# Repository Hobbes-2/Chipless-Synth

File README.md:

A cool chipless synth PCB! Made for the Chipless ysws.

Pictures:

BOM:

|Index|Quantity|Part Number     |Manufacturer Part Number|Description                    |Customer Reference|Available|Backorder|Unit Price|Extended Price USD|Link                                                                                                         |
|-----|--------|----------------|------------------------|-------------------------------|------------------|---------|---------|----------|------------------|-------------------------------------------------------------------------------------------------------------|
|1    |3       |4878-2N3904CT-ND|2N3904                  |TRANS NPN 40V 0.2A TO-92       |                  |3        |0        |0.14      |0.42              |https://www.digikey.com/en/products/detail/diotec-semiconductor/2N3904/13164701                              |
|2    |1       |CP-3523SJCT-ND  |SJ-3523-SMT-TR          |CONN JACK STEREO 3.5MM SMD R/A |                  |1        |0        |0.88      |0.88              |https://www.digikey.com/en/products/detail/same-sky-formerly-cui-devices/SJ-3523-SMT-TR/281297               |
|3    |1       |277-1247-ND     |1729128                 |TERM BLK 2P SIDE ENT 5.08MM PCB|                  |1        |0        |0.95      |0.95              |https://www.digikey.com/en/products/detail/phoenix-contact/1729128/260615                                    |
|4    |3       |445-2510-1-ND   |C1608X8R2A103K080AA     |CAP CER 10000PF 100V X8R 0603  |                  |3        |0        |0.14      |0.42              |https://www.digikey.com/en/products/detail/tdk/C1608X8R2A103K080AA/927136                                    |
|5    |1       |587-6004-1-ND   |EMK107B7104KAHT         |CAP CER 0.1UF 16V X7R 0603     |                  |1        |0        |0.1       |0.1               |https://www.digikey.com/en/products/detail/taiyo-yuden/EMK107B7104KAHT/7404019                               |
|6    |1       |311-4.70KMCT-ND |RC0201FR-074K7L         |RES 4.7K OHM 1% 1/20W 0201     |                  |1        |0        |0.1       |0.1               |https://www.digikey.com/en/products/detail/yageo/RC0201FR-074K7L/1948894                                     |
|7    |3       |YAG3413CT-ND    |AC0201FR-0710KL         |RES SMD 10K OHM 1% 1/20W 0201  |                  |3        |0        |0.1       |0.3               |https://www.digikey.com/en/products/detail/yageo/AC0201FR-0710KL/5894228                                     |
|8    |1       |987-1708-ND     |P0915N-EC15BR100K       |POT 100K OHM 1/20W PLASTIC LIN |                  |1        |0        |2.83      |2.83              |https://www.digikey.com/en/products/detail/tt-electronics-bi/P0915N-EC15BR100K/5957452?utm_source=chatgpt.com|
|9    |1       |401-1999-1-ND   |JS102011SAQN            |SWITCH SLIDE SPDT 300MA 6V     |                  |1        |0        |0.85      |0.85              |https://www.digikey.com/en/products/detail/c-k/JS102011SAQN/1640095?utm_source=chatgpt.com                   |

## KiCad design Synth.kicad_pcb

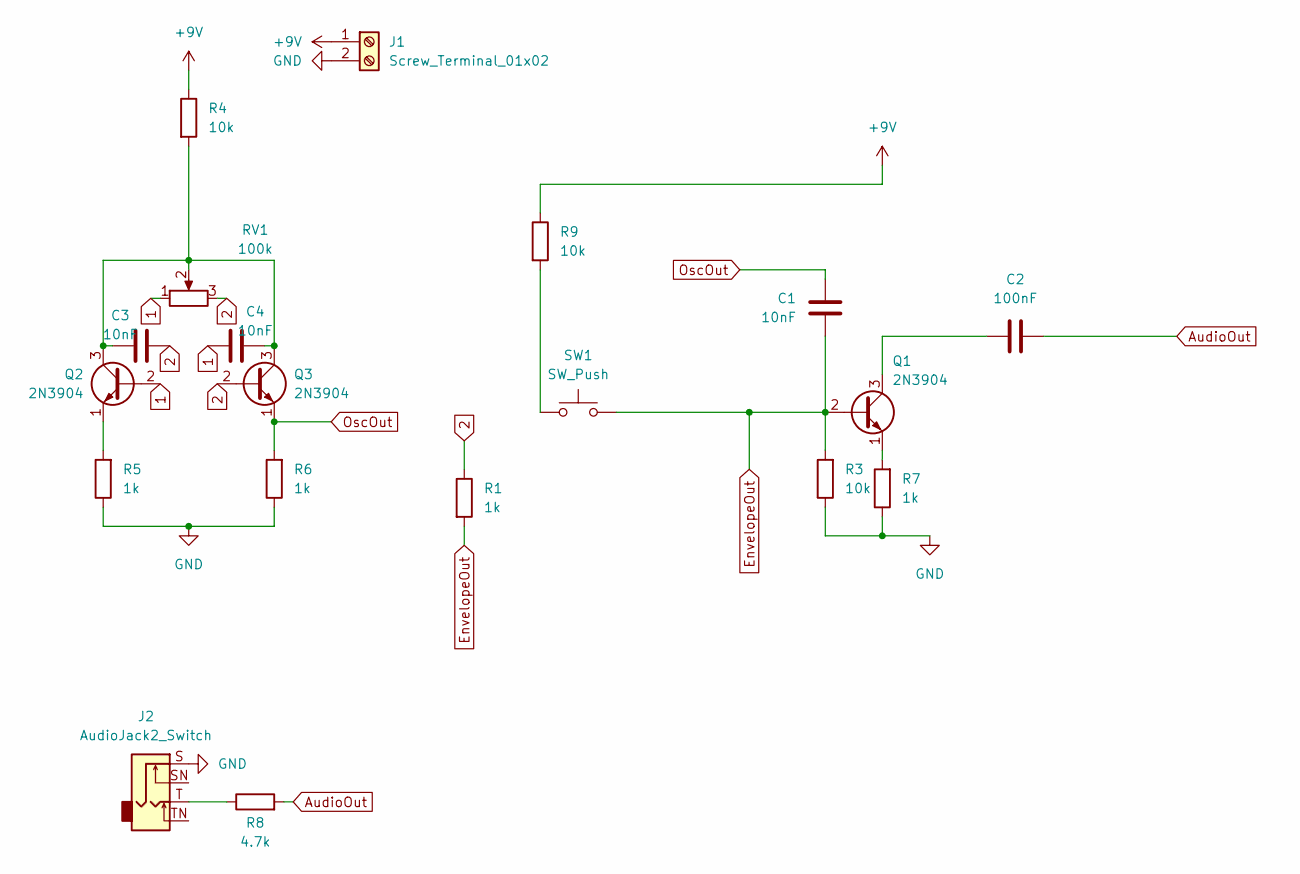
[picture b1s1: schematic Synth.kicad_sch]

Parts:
C1, C3, C4: 10nF; C_0603_1608Metric
C2: 100nF; C_0603_1608Metric
J1: Screw_Terminal_01x02; TerminalBlock_Phoenix_PT-1,5-2-5.0-H_1x02_P5.00mm_Horizontal
J2: AudioJack2_Switch; Jack_3.5mm_CUI_SJ-3523-SMT_Horizontal
Q1, Q2, Q3: 2N3904; TO-92_Inline
R1, R5, R6, R7: 1k; R_0201_0603Metric
R3, R4, R9: 10k; R_0201_0603Metric
R8: 4.7k; R_0201_0603Metric
RV1: 100k; Potentiometer_TT_P0915N
SW1: SW_Push; SW_SPDT_CK_JS102011SAQN

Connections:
1: C4.2, Q2.2 (B), RV1.1
2: C3.1, Q3.2 (B), R1.1, RV1.3
+9V: J1.1, R4.1, R9.1
AudioOut: C2.2, R8.2
EnvelopeOut: C1.2, Q1.2 (B), R1.2, R3.2, SW1.2
GND: J1.2, J2.S, R3.1, R5.1, R6.1, R7.1
unnamed: J2.T, R8.1
unnamed: C2.1, Q1.3 (C)
unnamed: Q1.1 (E), R7.2
unnamed: C3.2, C4.1, Q2.3 (C), Q3.3 (C), R4.2, RV1.2
unnamed: Q2.1 (E), R5.2
unnamed: R9.2, SW1.1
OscOut: C1.1, Q3.1 (E), R6.2

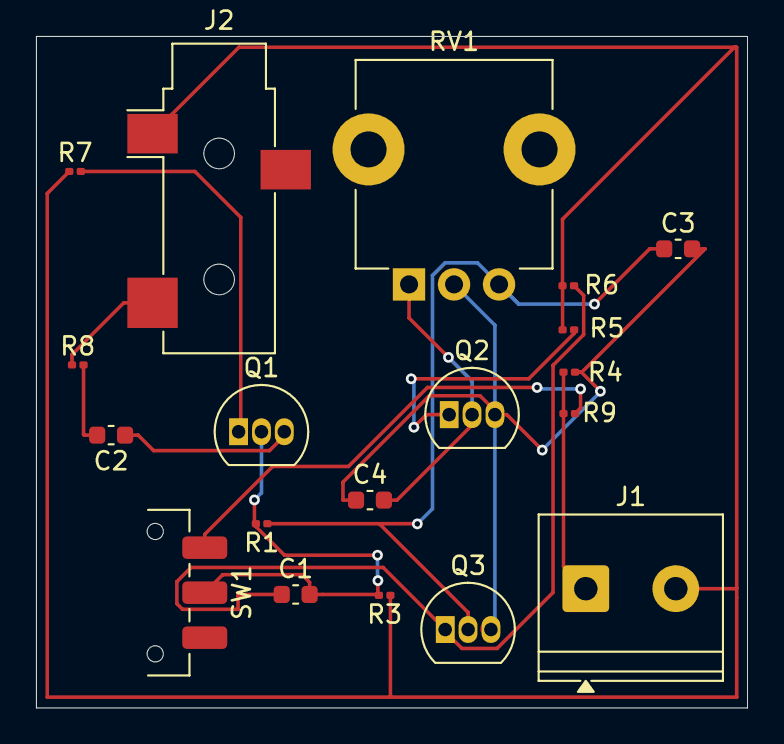
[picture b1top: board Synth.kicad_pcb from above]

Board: 2 copper layers, 39.5 x 37.3 mm, 19 parts (0 on the bottom side), 13 nets.

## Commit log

2026-06-18 adding files
2026-06-18 finishing up - i dont remember if i added files after adding the battery box thing
2026-06-19 added bom and fixed a resistor value in the schem - also added gerber
2026-06-19 update bom with links
2026-06-19 Organized files into folders
2026-06-19 Added readme with bom and pictures
    Added a README file detailing the chipless synth PCB, including images and a bill of materials (BOM) with part specifications and links.
2026-06-19 Tried to fix format issues for readme text
